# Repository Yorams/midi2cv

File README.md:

# midi2cv

I forked this repository from elkayem, original found here: https://github.com/elkayem/midi2cv. I wanted to make an PCB from this schematic and needed to ajust a couple parts to match the right footprint on the PCB. 

The MIDI to CV converter includes the following outputs:

* Note CV output (88 keys, 1V/octave) using a 12-bit DAC
* Note priority (highest note, lowest note, or last note) selectable with jumper or 3-way switch
* Velocity CV output (0 to 4V)
* 2x Control Change CV outout (0 to 4V) (i changed the pitch bend to CC2 for 2 control channels)
* Trigger output (5V, 20 msec pulse for each new key played)
* Gate output (5V when any key depressed)
* Clock output (1 clock per quarter note, 20 msec 5V pulses)

## Parts
* Arduino Nano
* Optocoupler (I used a Vishay SFH618A, but there are plenty of alternatives out there)
* 2x MCP4822 12-bit DACs
* LM324N Quad Op Amp 
* Diode (e.g., 1N917)
* 220, 500, 3x1K, 7.7K (3K+4.7K), 10K Ohm resistors
* 3x 0.1 uF ceramic capacitors
* 3,5mm jack panel mount for MIDI over TRS
* 7x 3,5mm jack PCB mount Horizontal (farnell code: 2518188)
* 3-pin header and jumper *or* 3-way switch
* 3-pin header to connect MIDI-In

The Arduino code uses the standard MIDI and SPI libraries, which can be found in the Arduino Library Manager. 

The schematic is illustrated at the bottom of this page (Eagle file included).  Input power (VIN) is 9-12V.  This is required for the Note CV op amp, used for the 0-7.3V note output.  1% metal film resistors are recommended for the 7.7K and 10K resistors, for a constant op-amp gain that does not change with temperature.  Note that 7.7K is not a standard resistor value.  I used a 3K and a 4.7K resistor in series, which are much more common values.  If precise tuning is desired, a trim pot can be added *or* the constant NOTE_SF can be adjusted in the code.  I opted for the latter.

Note priority is selected using a jumper attached to the three-pin header labelled NP_SEL in the schematic.  This header connects to the Arduino pins A0 and A2, with the center pin attached to ground.  Alternatively, a 3-way switch can be attached to this header. 

The note priority options and jumper configuration are as follows:
* **Highest Note:** When multiple notes are sounded simultaneously, the highest note being held will be sounded.  When the highest note is released, the next highest note will be played, and so on.  Remove the NP_SEL jumper to select this configuration.
* **Lowest Note:** Analagous to highest note, except the lowest note being held will be sounded. Connect the NP_SEL jumper to the A0 pin and center pin (ground) to select this configuration. 
* **Last Note:** The most recent note played will be sounded.  When that note is released, the next most recent note still being held will be sounded.  Connect the NP_SEL jumper to the A2 pin and center pin (ground) to select this configuration.

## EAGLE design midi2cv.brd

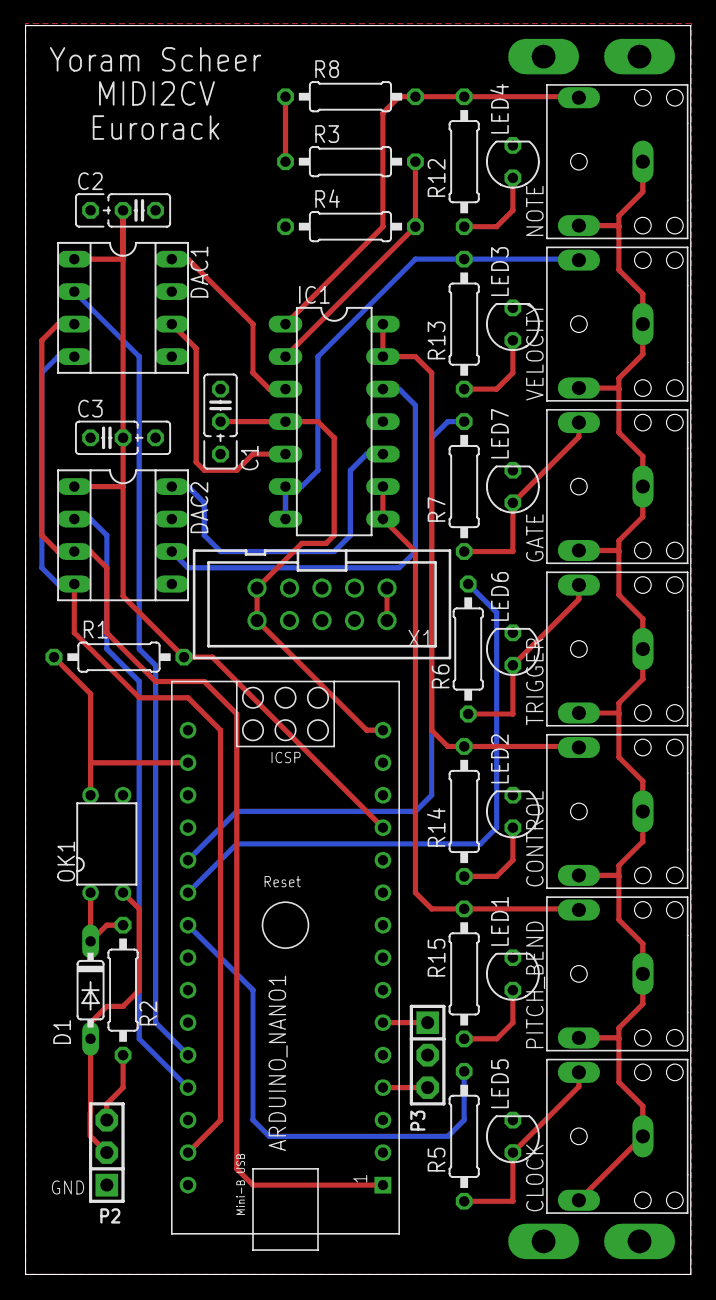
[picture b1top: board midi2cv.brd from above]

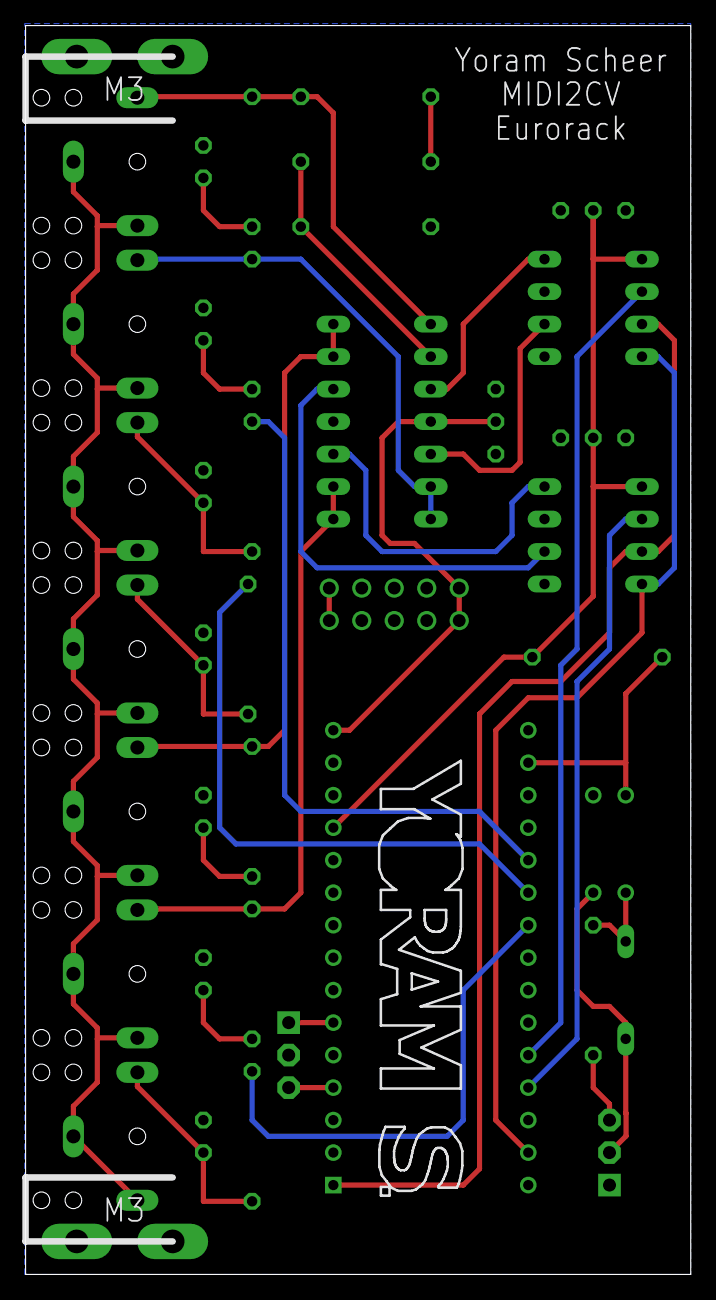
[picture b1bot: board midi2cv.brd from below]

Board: 2 copper layers, 52.0 x 97.6 mm, 41 parts (2 on the bottom side), 34 nets.

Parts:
ARDUINO_NANO1: ARDUINO_NANO
C1, C2, C3: 0.1uF; C025_050-025X075
CLOCK: 3.5_JACK_HORIZONTAL
CONTROL: 3.5_JACK_HORIZONTAL
D1: 1N4148; DO35-7
DAC1, DAC2: MCP4822; SOCKET-08
DRILEGEND: DRILEGEND
GATE: 3.5_JACK_HORIZONTAL
IC1: LM324N; DIL14
LED1, LED2, LED3, LED4, LED5, LED6, LED7: LED3MM
NOTE: 3.5_JACK_HORIZONTAL
OK1: SFH618A-2; DIP4
P2: MIDI-IN; SIP-100-03-40
P3: NP SEL; SIP-100-03-40
PITCH_BEND: 3.5_JACK_HORIZONTAL
R1: 500; 0207/10
R2: 220; 0207/10
R3: 3K; 0207/10
R4: 10K; 0207/10
R5, R6, R7, R12, R13, R14, R15: 1K; 0207/10
R8: 4.7K; 0207/10
TRIGGER: 3.5_JACK_HORIZONTAL
U$1: SCREW_TERMINAL_SINGLELEFT; SCREW_TERM_SINGLE_LEFT
U$2: SCREW_TERMINAL_SINGLERIGHT; SCREW_TERM_SINGLE_RIGHT
VELOCITY: 3.5_JACK_HORIZONTAL
X1: POWER; PAK100/2500-10

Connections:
5V: ARDUINO_NANO1.12, C2.2, C3.2, DAC1.1, DAC2.1, R1.2
A0: ARDUINO_NANO1.4, P3.3
A2: ARDUINO_NANO1.6, P3.1
CLOCK: CLOCK.P$2, LED5.A, R5.2
CONTROL: CONTROL.P$2, IC1.13, IC1.14, R14.1
D2: ARDUINO_NANO1.20, R7.1
D3: ARDUINO_NANO1.21, R6.1
D4: ARDUINO_NANO1.22, R5.1
D8: ARDUINO_NANO1.26, DAC1.2
D9: ARDUINO_NANO1.27, DAC2.2
D11: ARDUINO_NANO1.29, DAC1.4, DAC2.4
D13: ARDUINO_NANO1.1, DAC1.3, DAC2.3
GATE: GATE.P$2, LED7.A, R7.2
GND: ARDUINO_NANO1.14, ARDUINO_NANO1.19, C1.1, C2.1, C3.1, CLOCK.P$1, CLOCK.P$5, CONTROL.P$1, CONTROL.P$5, DAC1.5, DAC1.7, DAC2.5, DAC2.7, GATE.P$1, GATE.P$5, IC1.11, LED1.K, LED2.K, LED3.K, LED4.K, LED5.K, LED6.K, LED7.K, NOTE.P$1, NOTE.P$5, OK1.3, P2.1, P3.2, PITCH_BEND.P$1, PITCH_BEND.P$5, R4.1, TRIGGER.P$1, TRIGGER.P$5, U$1.P$1, U$1.P$2, U$2.P$1, U$2.P$2, VELOCITY.P$1, VELOCITY.P$5, X1.3, X1.4, X1.5, X1.6, X1.7, X1.8
unnamed: D1.C, OK1.1, R2.2
unnamed: D1.A, OK1.2, P2.2
unnamed: P2.3, R2.1
unnamed: DAC1.8, IC1.3
unnamed: R3.2, R8.1
unnamed: IC1.2, R3.1, R4.2
unnamed: DAC1.6, IC1.5
unnamed: DAC2.8, IC1.10
unnamed: DAC2.6, IC1.12
unnamed: X1.1, X1.2
unnamed: LED4.A, R12.2
unnamed: LED3.A, R13.2
unnamed: LED2.A, R14.2
unnamed: LED1.A, R15.2
NOTE: IC1.1, NOTE.P$2, R8.2, R12.1
PITCH_BEND: IC1.8, IC1.9, PITCH_BEND.P$2, R15.1
RX0: ARDUINO_NANO1.17, OK1.4, R1.1
TRIGGER: LED6.A, R6.2, TRIGGER.P$2
VELOCITY: IC1.6, IC1.7, R13.1, VELOCITY.P$2
VIN: ARDUINO_NANO1.15, C1.2, IC1.4, X1.9, X1.10

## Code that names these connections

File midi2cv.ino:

/* 
 *    MIDI2CV 
 *    Copyright (C) 2017  Larry McGovern
 *  
 *    This program is free software: you can redistribute it and/or modify
 *    it under the terms of the GNU General Public License as published by
 *    the Free Software Foundation, either version 3 of the License, or
 *    (at your option) any later version.
 *
 *    This program is distributed in the hope that it will be useful,
 *    but WITHOUT ANY WARRANTY; without even the implied warranty of
 *    MERCHANTABILITY or FITNESS FOR A PARTICULAR PURPOSE.  See the
 *    GNU General Public License <http://www.gnu.org/licenses/> for more details.
 */
 
#include <MIDI.h>
#include <SPI.h>

// Note priority is set by pins A0 and A2
// Highest note priority: A0 and A2 high (open)
// Lowest note priority:  A0 low (ground), A2 high (open)
// Last note priority:    A2 low (ground)
 
#define NP_SEL1 A0  // Note priority is set by pins A0 and A2
#define NP_SEL2 A2  

#define GATE  2
#define TRIG  3
#define CLOCK 4
#define DAC1  8 
#define DAC2  9

MIDI_CREATE_DEFAULT_INSTANCE();

void setup()
{
 pinMode(NP_SEL1, INPUT_PULLUP);
 pinMode(NP_SEL2, INPUT_PULLUP);
 
 pinMode(GATE, OUTPUT);
 pinMode(TRIG, OUTPUT);
 pinMode(CLOCK, OUTPUT);
 pinMode(DAC1, OUTPUT);
 pinMode(DAC2, OUTPUT);
 digitalWrite(GATE,LOW);
 digitalWrite(TRIG,LOW);
 digitalWrite(CLOCK,LOW);
 digitalWrite(DAC1,HIGH);
 digitalWrite(DAC2,HIGH);
 

 SPI.begin();

 MIDI.begin(MIDI_CHANNEL_OMNI);

 // Set initial pitch bend voltage to 0.5V (mid point).  With Gain = 1X, this is 1023
 // Other DAC outputs will come up as 0V, so don't need to be initialized
 setVoltage(DAC2, 0, 0, 1023);  
}

bool notes[88] = {0}; 
int8_t noteOrder[20] = {0}, orderIndx = {0};
unsigned long trigTimer = 0;

void loop()
{
  int type, noteMsg, velocity, channel, d1, d2;
  static unsigned long clock_timer=0, clock_timeout=0;
  static unsigned int clock_count=0;
  bool S1, S2;

  if ((trigTimer > 0) && (millis() - trigTimer > 20)) { 
    digitalWrite(TRIG,LOW); // Set trigger low after 20 msec 
    trigTimer = 0;  
  }

  if ((clock_timer > 0) && (millis() - clock_timer > 20)) { 
    digitalWrite(CLOCK,LOW); // Set clock pulse low after 20 msec 
    clock_timer = 0;  
  }
  
  if (MIDI.read()) {                    
    byte type = MIDI.getType();
    switch (type) {
      case midi::NoteOn: 
      case midi::NoteOff:
        noteMsg = MIDI.getData1() - 21; // A0 = 21, Top Note = 108
        channel = MIDI.getChannel();
        
        if ((noteMsg < 0) || (noteMsg > 87)) break; // Only 88 notes of keyboard are supported

        if (type == midi::NoteOn) velocity = MIDI.getData2();
        else velocity  = 0;  

        if (velocity == 0)  {
          notes[noteMsg] = false;
        }
        else {
          notes[noteMsg] = true;
          // velocity range from 0 to 4095 mV  Left shift d2 by 5 to scale from 0 to 4095, 
          // and choose gain = 2X
          setVoltage(DAC1, 1, 1, velocity<<5);  // DAC1, channel 1, gain = 2X
        }

        // Pins NP_SEL1 and NP_SEL2 indictate note priority
        S1 = digitalRead(NP_SEL1);
        S2 = digitalRead(NP_SEL2);

        if (S1 && S2) { // Highest note priority
          commandTopNote();
        }
        else if (!S1 && S2) { // Lowest note priority
          commandBottomNote();
        }
        else { // Last note priority
           if (notes[noteMsg]) {  // If note is on and using last note priority, add to ordered list
            orderIndx = (orderIndx+1) % 20;
            noteOrder[orderIndx] = noteMsg;                 
          }
          commandLastNote();         
        }
        break;
        
      case midi::PitchBend:
        d1 = MIDI.getData1();
        d2 = MIDI.getData2(); // d2 from 0 to 127, mid point = 64

        // Pitch bend output from 0 to 1023 mV.  Left shift d2 by 4 to scale from 0 to 2047.
        // With DAC gain = 1X, this will yield a range from 0 to 1023 mV.  
        //setVoltage(DAC2, 0, 0, d2<<4);  // DAC2, channel 0, gain = 1X
        
        break;

      case midi::ControlChange: 
        d1 = MIDI.getData1();
        d2 = MIDI.getData2(); // From 0 to 127

        // CC range from 0 to 4095 mV  Left shift d2 by 5 to scale from 0 to 4095, 
        // and choose gain = 2X
        
        if(d1 == 1){
          setVoltage(DAC2, 1, 1, d2<<5);  // DAC2, channel 1, gain = 2X
        }
        if(d1 == 2){
          setVoltage(DAC2, 0, 1, d2<<5);  // DAC2, channel 0, gain = 1X
        }
        
        break;
        
      case midi::Clock:
        if (millis() > clock_timeout + 300) clock_count = 0; // Prevents Clock from starting in between quarter notes after clock is restarted!
        clock_timeout = millis();
        
        if (clock_count == 0) {
          digitalWrite(CLOCK,HIGH); // Start clock pulse
          clock_timer=millis();    
        }
        clock_count++;
        if (clock_count == 24) {  // MIDI timing clock sends 24 pulses per quarter note.  Sent pulse only once every 24 pulses
          clock_count = 0;  
        }
        break;
        
      case midi::ActiveSensing: 
        break;
        
      default:
        d1 = MIDI.getData1();
        d2 = MIDI.getData2();
    }
  }
}

void commandTopNote()
{
  int topNote = 0;
  bool noteActive = false;
  
  for (int i=0; i<88; i++)
  {
    if (notes[i]) {
      topNote = i;
      noteActive = true;
    }
  }

  if (noteActive) 
    commandNote(topNote);
  else // All notes are off, turn off gate
    digitalWrite(GATE,LOW);  
}

void commandBottomNote()
{
  int bottomNote = 0;
  bool noteActive = false;
 
  for (int i=87; i>=0; i--)
  {
    if (notes[i]) {
      bottomNote = i;
      noteActive = true;
    }
  }

  if (noteActive) 
    commandNote(bottomNote);
  else // All notes are off, turn off gate
    digitalWrite(GATE,LOW);
}

void commandLastNote()
{

  int8_t noteIndx;
  
  for (int i=0; i<20; i++) {
    noteIndx = noteOrder[ mod(orderIndx-i, 20) ];
    if (notes[noteIndx]) {
      commandNote(noteIndx);
      return;
    }
  }
  digitalWrite(GATE,LOW);  // All notes are off
}

// Rescale 88 notes to 4096 mV:
//    noteMsg = 0 -> 0 mV 
//    noteMsg = 87 -> 4096 mV
// DAC output will be (4095/87) = 47.069 mV per note, and 564.9655 mV per octive
// Note that DAC output will need to be amplified by 1.77X for the standard 1V/octave 

#define NOTE_SF 47.069f // This value can be tuned if CV output isn't exactly 1V/octave

void commandNote(int noteMsg) {
  digitalWrite(GATE,HIGH);
  digitalWrite(TRIG,HIGH);
  trigTimer = millis();
  
  unsigned int mV = (unsigned int) ((float) noteMsg * NOTE_SF + 0.5); 
  setVoltage(DAC1, 0, 1, mV);  // DAC1, channel 0, gain = 2X
}

// setVoltage -- Set DAC voltage output
// dacpin: chip select pin for DAC.  Note and velocity on DAC1, pitch bend and CC on DAC2
// channel: 0 (A) or 1 (B).  Note and pitch bend on 0, velocity and CC on 2.
// gain: 0 = 1X, 1 = 2X.  
// mV: integer 0 to 4095.  If gain is 1X, mV is in units of half mV (i.e., 0 to 2048 mV).
// If gain is 2X, mV is in units of mV

void setVoltage(int dacpin, bool channel, bool gain, unsigned int mV)
{
  unsigned int command = channel ? 0x9000 : 0x1000;

  command |= gain ? 0x0000 : 0x2000;
  command |= (mV & 0x0FFF);
  
  SPI.beginTransaction(SPISettings(8000000, MSBFIRST, SPI_MODE0));
  digitalWrite(dacpin,LOW);
  SPI.transfer(command>>8);
  SPI.transfer(command&0xFF);
  digitalWrite(dacpin,HIGH);
  SPI.endTransaction();
}

int mod(int a, int b)
{
    int r = a % b;
    return r < 0 ? r + b : r;
}

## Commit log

2020-03-30 Changed parts for PCB
    Changed a couple of parts for the PCB design.
2020-03-30 Added PCB design
2020-03-30 Changed filename to match .sch
2020-03-30 Changed the pitch bend to CC2

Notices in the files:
parts and their libraries:
con-headers-jp: Copyright (C) 2008, Bob Starr
